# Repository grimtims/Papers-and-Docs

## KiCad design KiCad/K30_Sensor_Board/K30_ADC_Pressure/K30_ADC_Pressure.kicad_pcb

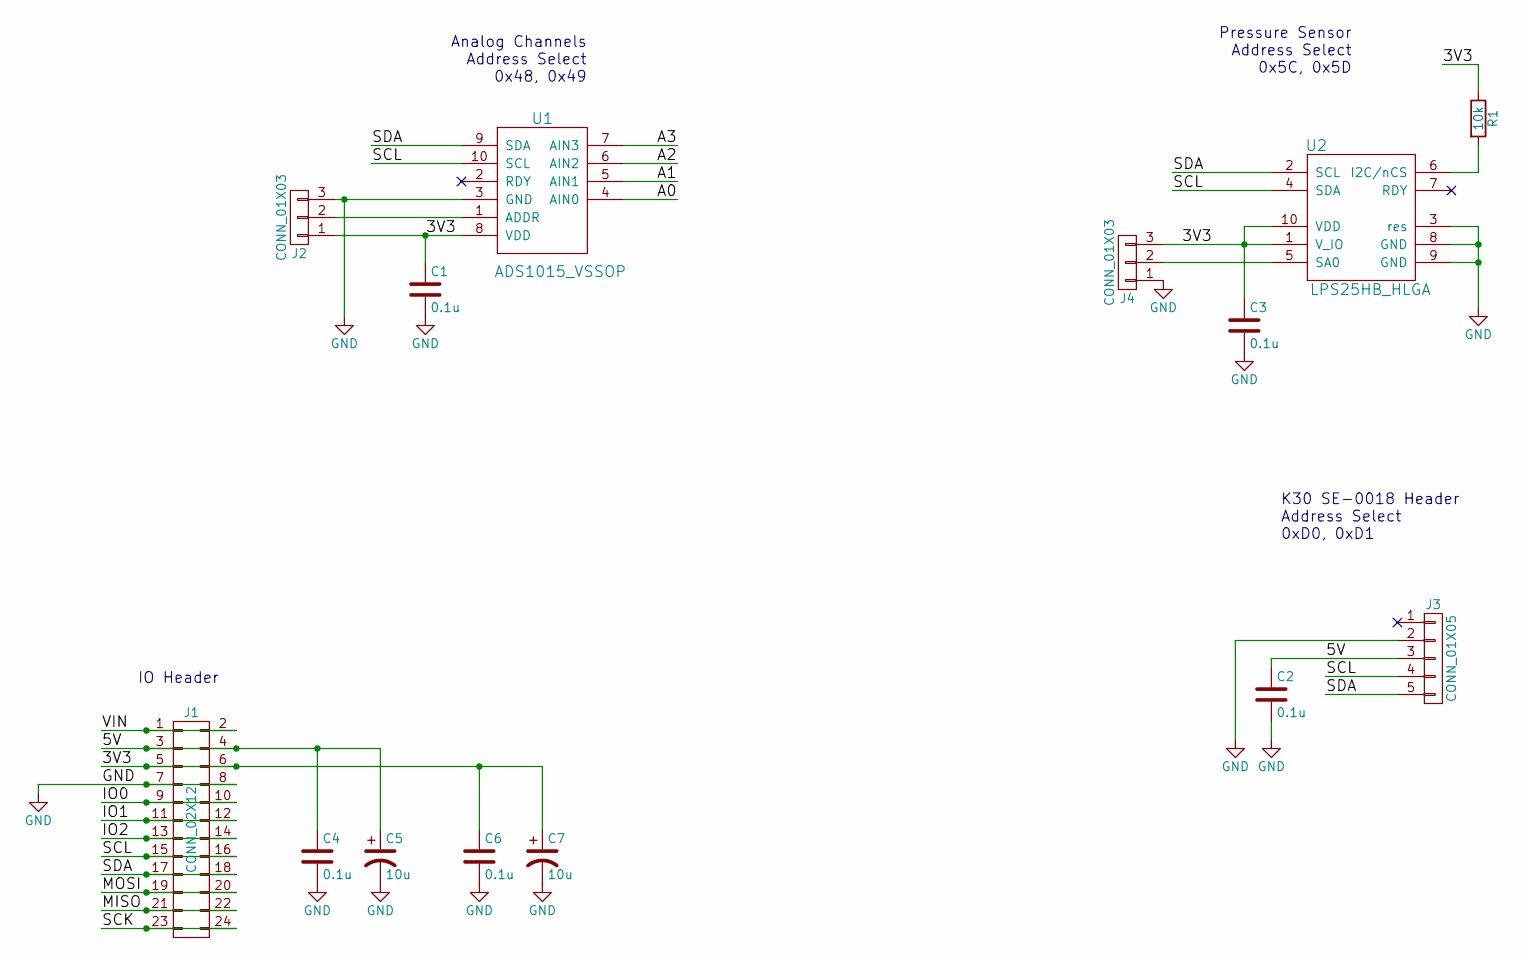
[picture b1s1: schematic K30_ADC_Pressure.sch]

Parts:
C1, C2, C3, C4, C6: 0.1u; C_0603_HandSoldering
C5, C7: 10u; CP_Elec_5x4.5
J1: CONN_02X12; Socket_Strip_Straight_2x12_Pitch2.54mm
J2, J4: CONN_01X03; Socket_Strip_Straight_1x03_Pitch2.54mm
J3: CONN_01X05; Socket_Strip_Straight_1x05_Pitch2.54mm
R1: 10k; R_0603_HandSoldering
U1: ADS1015_VSSOP; MSOP-10_3x3mm_Pitch0.5mm
U2: LPS25HB_HLGA; HLGA10L

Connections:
/3V3: C1.1, C3.1, C6.1, C7.1, J1.5, J1.6, J2.1, J4.3, R1.1, U1.8 (VDD), U2.1 (V_IO), U2.10 (VDD)
/5V: C2.1, C4.1, C5.1, J1.3, J1.4, J3.3
/A0: U1.4 (AIN0)
/A1: U1.5 (AIN1)
/A2: U1.6 (AIN2)
/A3: U1.7 (AIN3)
/IO0: J1.9, J1.10
/IO1: J1.11, J1.12
/IO2: J1.13, J1.14
/MISO: J1.21, J1.22
/MOSI: J1.19, J1.20
/SCK: J1.23, J1.24
/SCL: J1.15, J1.16, J3.4, U1.10 (SCL), U2.4 (SDA)
/SDA: J1.17, J1.18, J3.5, U1.9 (SDA), U2.2 (SCL)
/VIN: J1.1, J1.2
GND: C1.2, C2.2, C3.2, C4.2, C5.2, C6.2, C7.2, J1.7, J1.8, J2.3, J3.2, J4.1, U1.3 (GND), U2.3 (res), U2.8 (GND), U2.9 (GND)
unnamed: J2.2, U1.1 (ADDR)
unnamed: J4.2, U2.5 (SA0)
unnamed: R1.2, U2.6 (I2C/nCS)

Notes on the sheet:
IO Header
Pressure Sensor Address Select 0x5C, 0x5D
Analog Channels Address Select 0x48, 0x49
K30 SE-0018 Header Address Select 0xD0, 0xD1

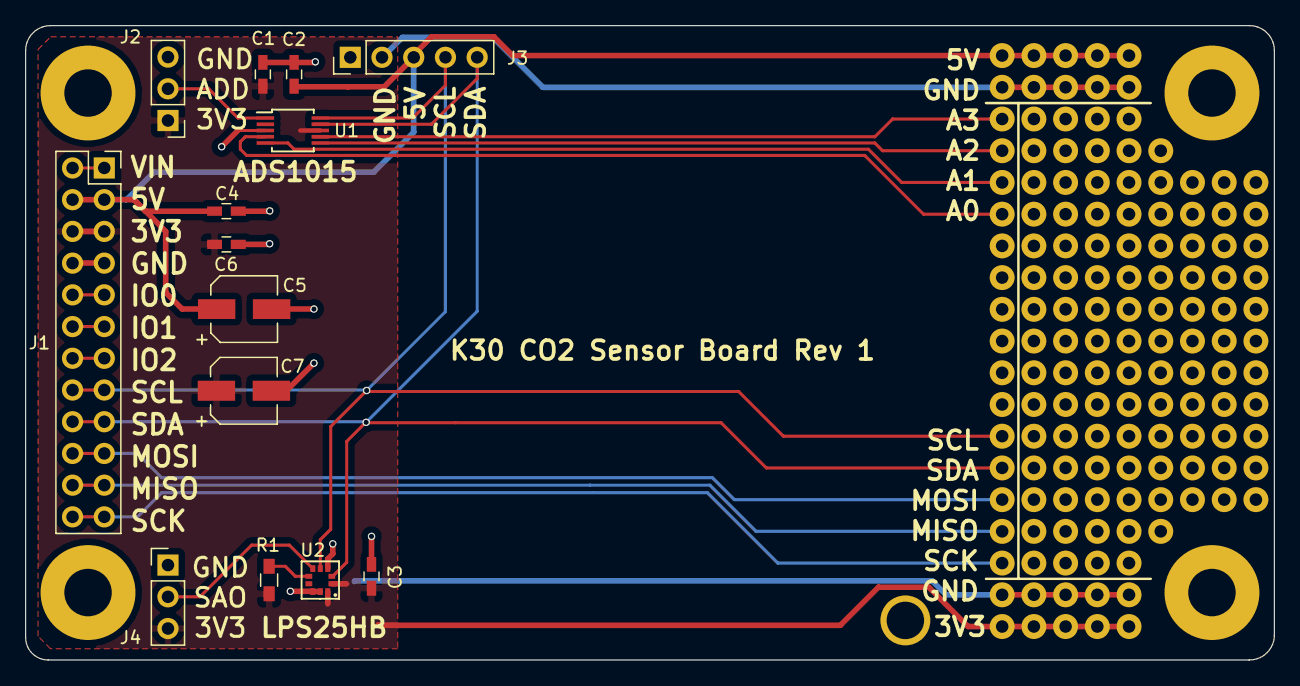
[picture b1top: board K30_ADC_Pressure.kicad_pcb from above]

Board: 2 copper layers, 100.0 x 50.8 mm, 14 parts (0 on the bottom side), 15 nets.

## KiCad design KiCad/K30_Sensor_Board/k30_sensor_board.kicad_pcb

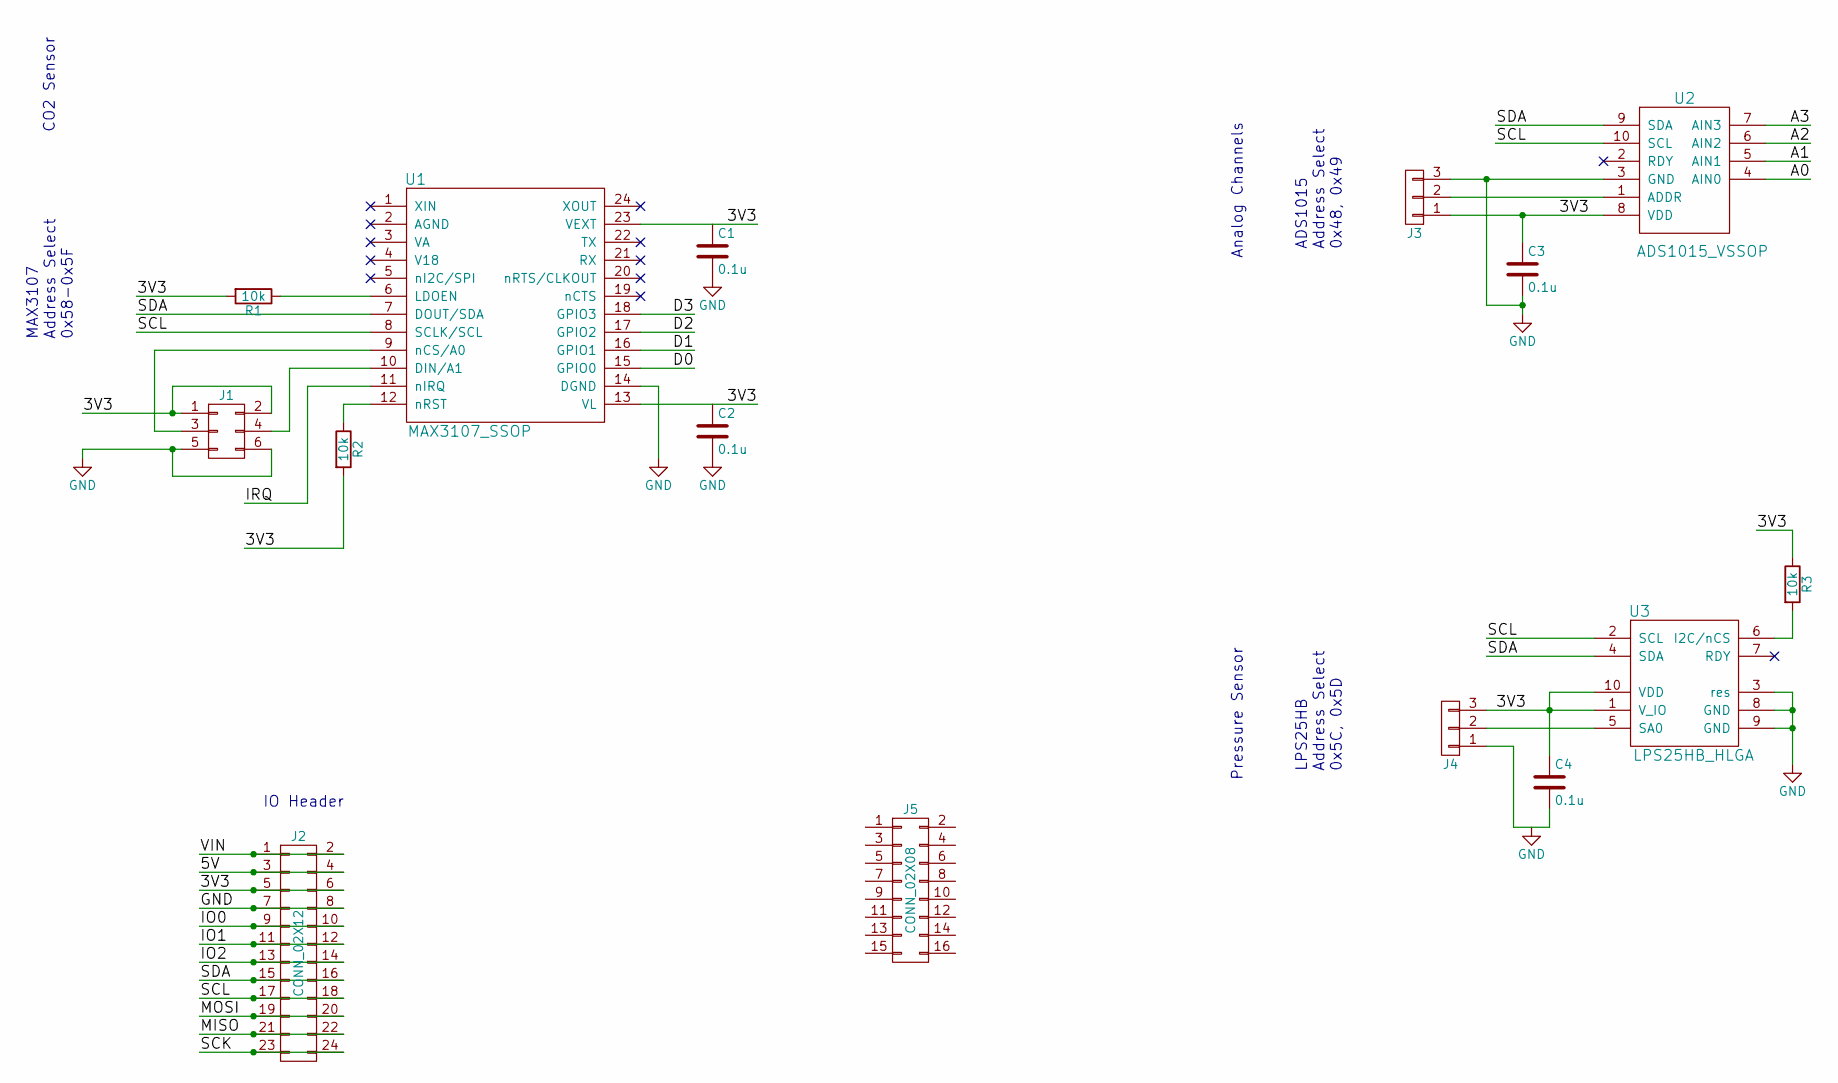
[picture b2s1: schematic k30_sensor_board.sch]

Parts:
C1, C2, C3, C4: 0.1u; C_0603_HandSoldering
J1: CONN_02X03; Pin_Header_Straight_2x03_Pitch2.00mm
J2: CONN_02X12; Pin_Header_Straight_2x12_Pitch2.00mm
J3, J4: CONN_01X03; Pin_Header_Straight_1x03_Pitch2.00mm
J5: CONN_02X08; Pin_Header_Straight_2x08_Pitch2.00mm
R1, R2, R3: 10k; R_0603_HandSoldering
U1: MAX3107_SSOP; SSOP-24_5.3x8.2mm_Pitch0.65mm
U2: ADS1015_VSSOP; MSOP-10-1EP_3x3mm_Pitch0.5mm
U3: LPS25HB_HLGA; HLGA10L

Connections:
/3V3: C3.1, C4.1, J1.1, J1.2, J2.5, J2.6, J3.1, J4.3, R1.2, R2.2, R3.1, U1.13 (VL), U1.23 (VEXT), U2.8 (VDD), U3.1 (V_IO), U3.10 (VDD)
/5V: J2.3, J2.4
/A0: U2.4 (AIN0)
/A1: U2.5 (AIN1)
/A2: U2.6 (AIN2)
/A3: U2.7 (AIN3)
/D0: U1.15 (GPIO0)
/D1: U1.16 (GPIO1)
/D2: U1.17 (GPIO2)
/D3: U1.18 (GPIO3)
/IO0: J2.9, J2.10
/IO1: J2.11, J2.12
/IO2: J2.13, J2.14
/IRQ: U1.11 (nIRQ)
/MISO: J2.21, J2.22
/MOSI: J2.19, J2.20
/SCK: J2.23, J2.24
/SCL: J2.17, J2.18, U1.8 (SCLK/SCL), U2.10 (SCL), U3.2 (SCL)
/SDA: J2.15, J2.16, U1.7 (DOUT/SDA), U2.9 (SDA), U3.4 (SDA)
/VIN: J2.1, J2.2
unnamed: J1.3, U1.9 (nCS/A0)
unnamed: J1.4, U1.10 (DIN/A1)
unnamed: J3.2, U2.1 (ADDR)
unnamed: J4.2, U3.5 (SA0)
unnamed: R1.1, U1.6 (LDOEN)
unnamed: R2.1, U1.12 (nRST)
unnamed: R3.2, U3.6 (I2C/nCS)

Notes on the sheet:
Analog Channels
Pressure Sensor
CO2 Sensor
ADS1015 Address Select 0x48, 0x49
LPS25HB Address Select 0x5C, 0x5D
MAX3107 Address Select 0x58-0x5F
IO Header

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
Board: 2 copper layers, 14 parts (2 on the bottom side), 20 nets, no tracks yet.

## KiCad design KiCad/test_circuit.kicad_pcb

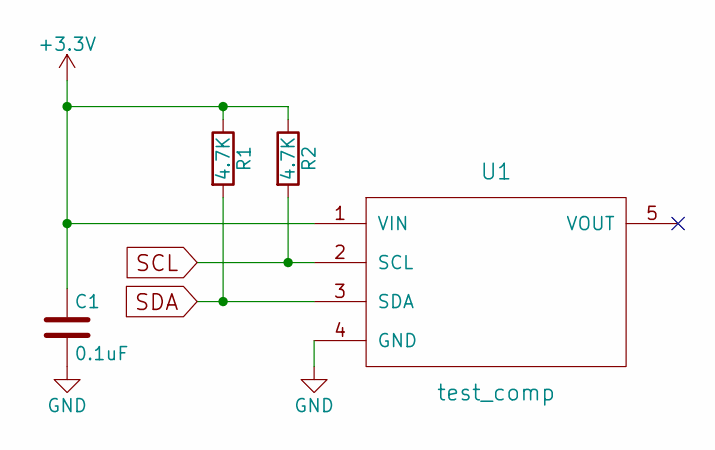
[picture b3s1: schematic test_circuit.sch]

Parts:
C1: 0.1uF; C_0201
R1, R2: 4.7K; R_0201
U1: test_comp; Conn-5

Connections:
+3V3: C1.1, R1.1, R2.1, U1.1 (VIN)
GND: C1.2, U1.4 (GND)
SCL: R2.2, U1.2 (SCL)
SDA: R1.2, U1.3 (SDA)

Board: 2 copper layers, 4 parts (0 on the bottom side), 4 nets, no tracks yet.

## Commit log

2017-06-27 KiCAD K30 CO2 sensor board project
2017-06-29 minor changes to mounting hole
2017-07-03 added other kicad projects, sketchup solar model
2017-07-03 added base plate to solar panel mount
2017-07-06 presentations added
2017-07-10 added decoupling capacitors for power input
2017-07-11 remove leds, new gerber files
2017-07-18 add inventory list
